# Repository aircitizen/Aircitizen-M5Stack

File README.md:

# m5stack

### Description

Here you'll find the CAD (STL+ F3d) for making your own shield, and the electronic shield (eagle + gerber file)

Component Name | Product link
------------ | -------------
M5 board |  https://amzn.to/2YmzmEy
Battery shield 700mAh  | https://amzn.to/2IX5oBG
Plantower PMSA003 | add link here.

 ###### Credit
Created by Vincent DUPUIS
with participation of :

Adel KHENICHE on Electronic production

Raphael BOYERO on 3D design.

#### Sources

Adafruit SHT31 | https://github.com/adafruit/Adafruit-SHT31-Sensor-Breakout-PCB

Adafruit Si7021 | https://learn.adafruit.com/adafruit-si7021-temperature-plus-humidity-sensor

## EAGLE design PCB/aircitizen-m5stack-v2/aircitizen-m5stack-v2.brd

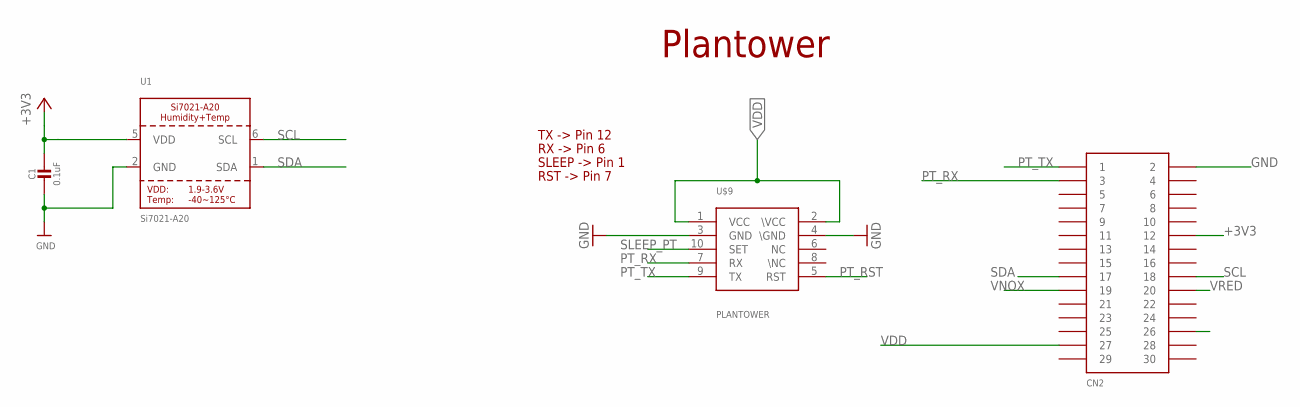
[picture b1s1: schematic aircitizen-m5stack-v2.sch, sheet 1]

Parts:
C1: 0.1uF; _1206
CN2: CON_PINHD-2X15; 2X15SMD
U1: Si7021-A20; DFN6_3X3_SI
U$9: PLANTOWER; CONN

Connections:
+3V3: C1.1, CN2.P$12 (12), U1.5 (VDD)
GND: C1.2, CN2.P$2 (2), U1.2 (GND), U$9.3 (GND), U$9.4 (\GND); also elsewhere on the board
PRE26: CN2.P$26 (26); also elsewhere on the board
PT_RST: U$9.5 (RST)
PT_RX: CN2.P$3 (3), U$9.7 (RX)
PT_TX: CN2.P$1 (1), U$9.9 (TX)
SCL: CN2.P$18 (18), U1.6 (SCL)
SDA: CN2.P$17 (17), U1.1 (SDA)
SLEEP_PT: U$9.10 (SET)
VDD: CN2.P$27 (27), U$9.1 (VCC), U$9.2 (\VCC); also elsewhere on the board
VNOX: CN2.P$19 (19); also elsewhere on the board
VRED: CN2.P$20 (20); also elsewhere on the board

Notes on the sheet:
Plantower
RX -> Pin 6
TX -> Pin 12
SLEEP -> Pin 1
RST -> Pin 7

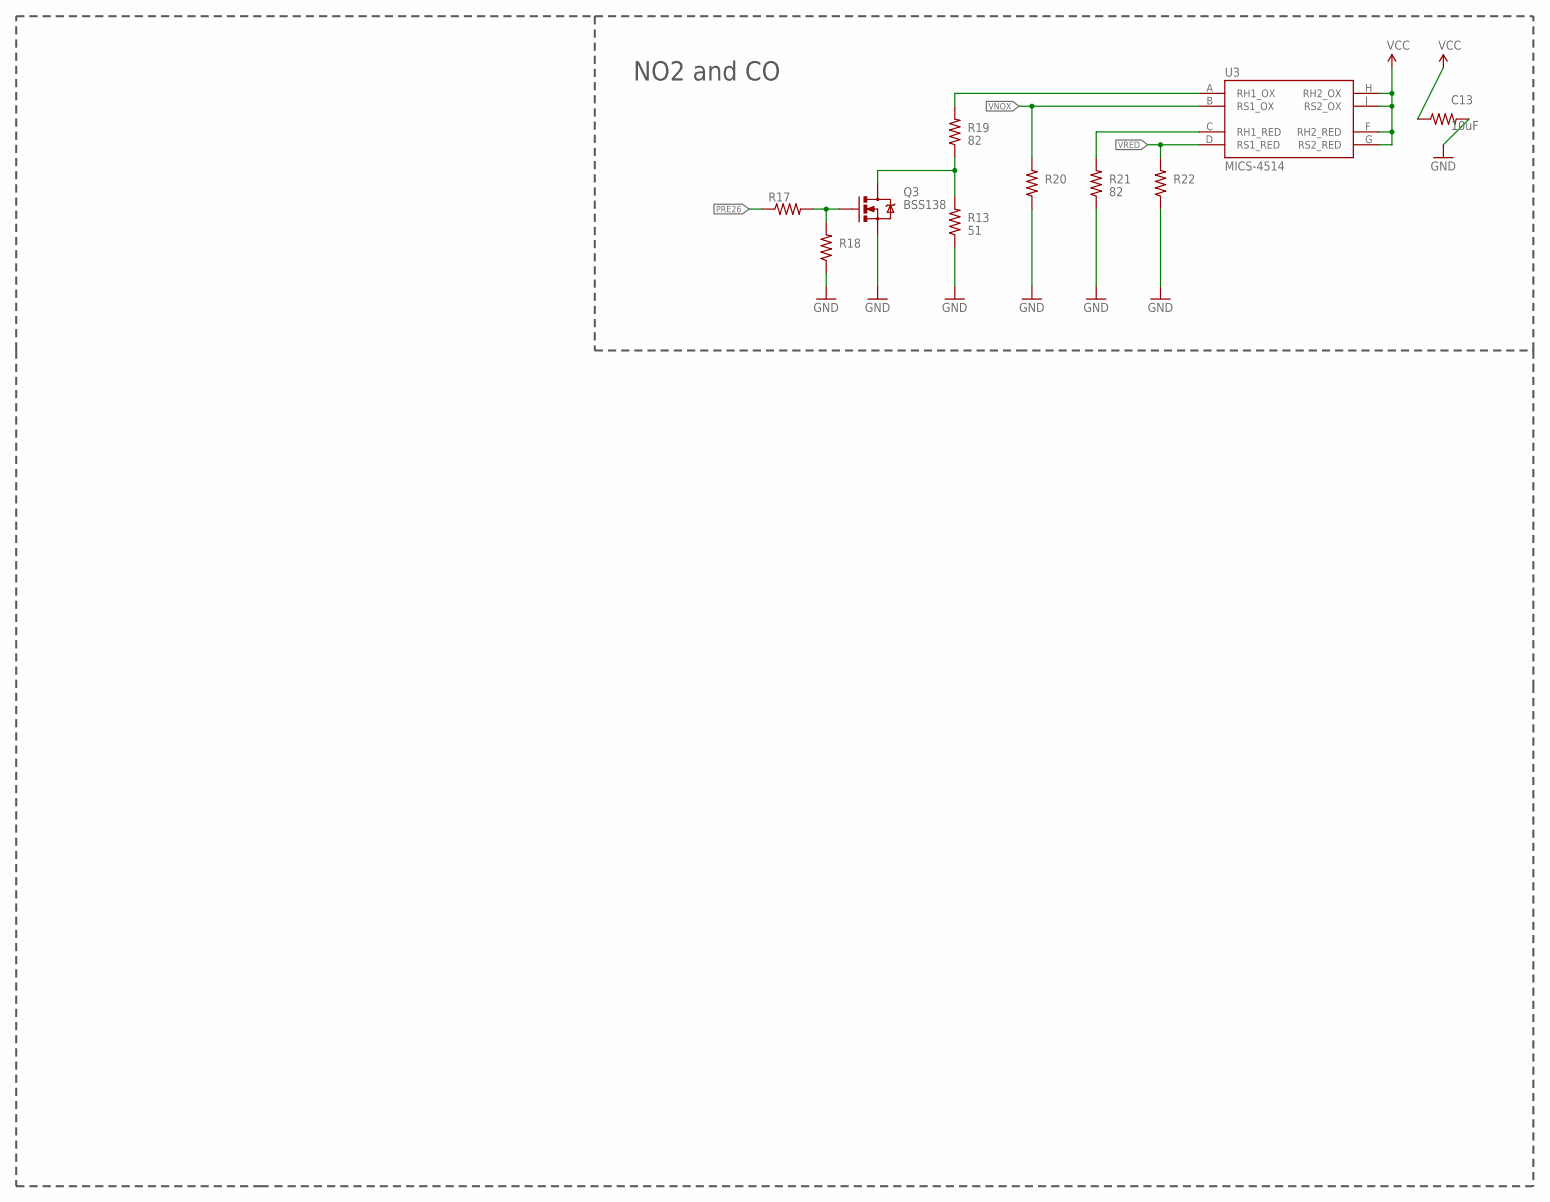
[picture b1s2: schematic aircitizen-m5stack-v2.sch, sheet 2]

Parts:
C13: 10uF; R1206FAB
Q3: MOSFET-NCHANNELBSS138; SOT23-3
R13: 51; R1206FAB
R17: 100; R1206FAB
R18: 100K; R1206FAB
R19, R21: 82; R1206FAB
R20: 22K; R1206FAB
R22: 47K; R1206FAB
U3: MICS-4514; MICS_10-SMD

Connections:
GND: C13.2, Q3.2 (S), R13.1, R18.1, R20.1, R21.1, R22.1; also elsewhere on the board
unnamed: Q3.3 (D), R13.2, R19.1
unnamed: Q3.1 (G), R17.2, R18.2
unnamed: R19.2, U3.A (RH1_OX)
unnamed: R21.2, U3.C (RH1_RED)
PRE26: R17.1; also elsewhere on the board
VDD: C13.1, U3.F (RH2_RED), U3.G (RS2_RED), U3.H (RH2_OX), U3.J (RS2_OX); also elsewhere on the board
VNOX: R20.2, U3.B (RS1_OX); also elsewhere on the board
VRED: R22.2, U3.D (RS1_RED); also elsewhere on the board

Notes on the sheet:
NO2 and CO

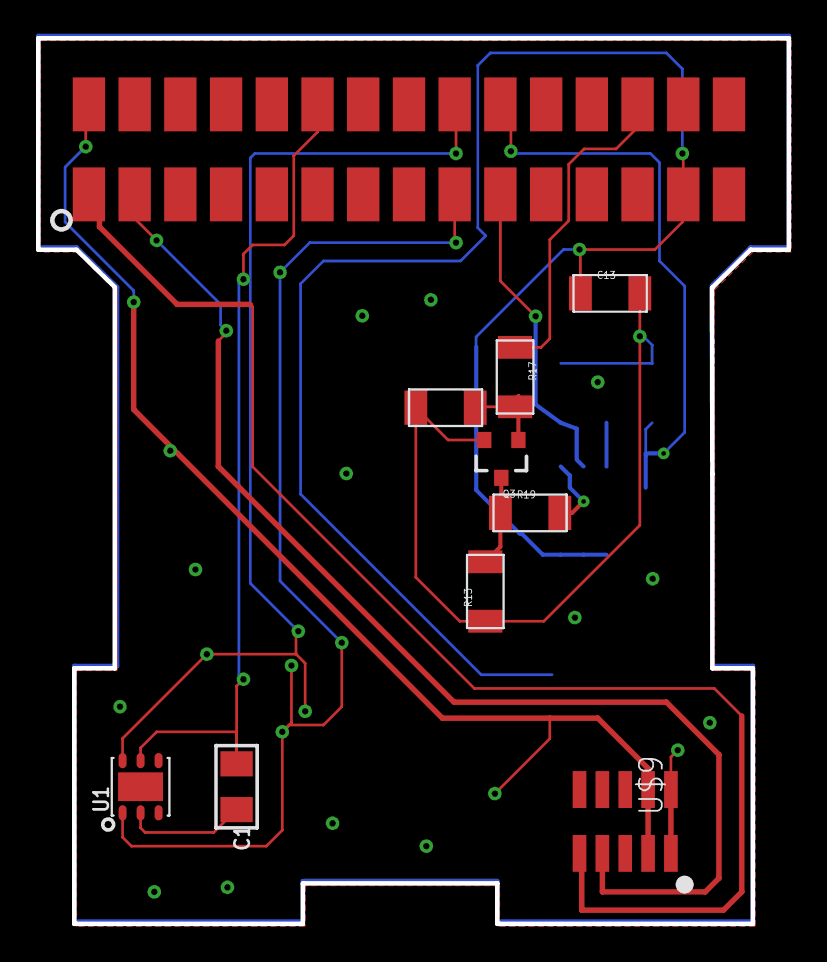
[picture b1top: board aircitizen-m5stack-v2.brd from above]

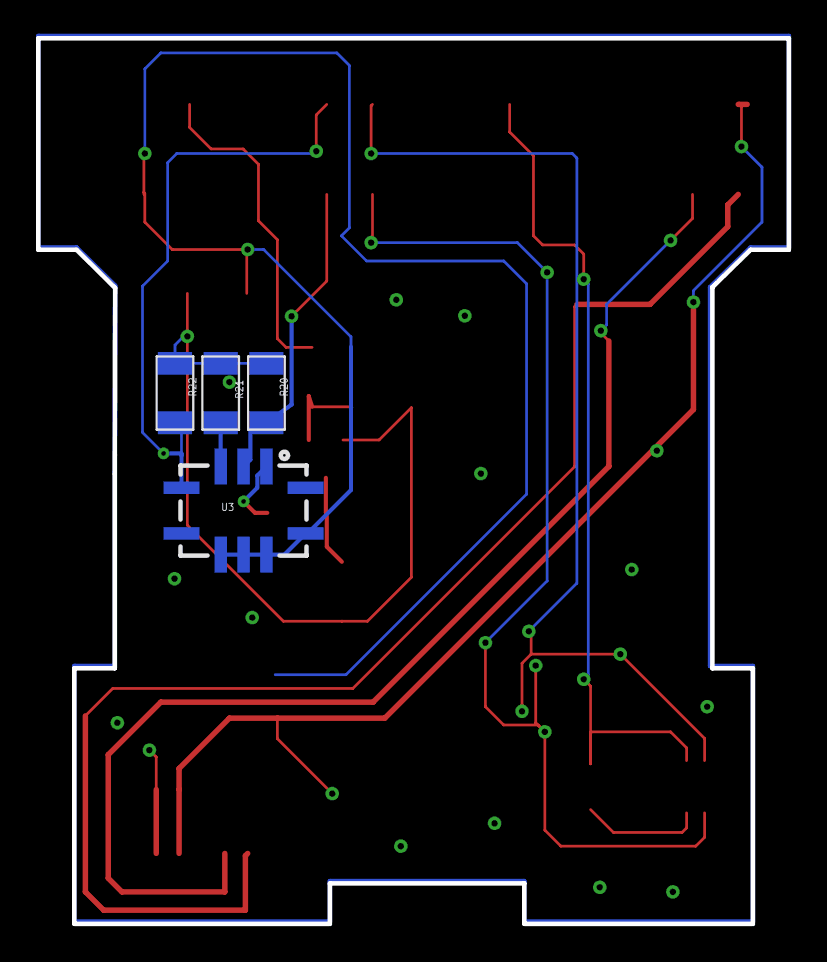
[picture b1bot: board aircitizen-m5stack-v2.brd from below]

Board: 2 copper layers, 41.7 x 49.2 mm, 14 parts (4 on the bottom side), 14 nets.

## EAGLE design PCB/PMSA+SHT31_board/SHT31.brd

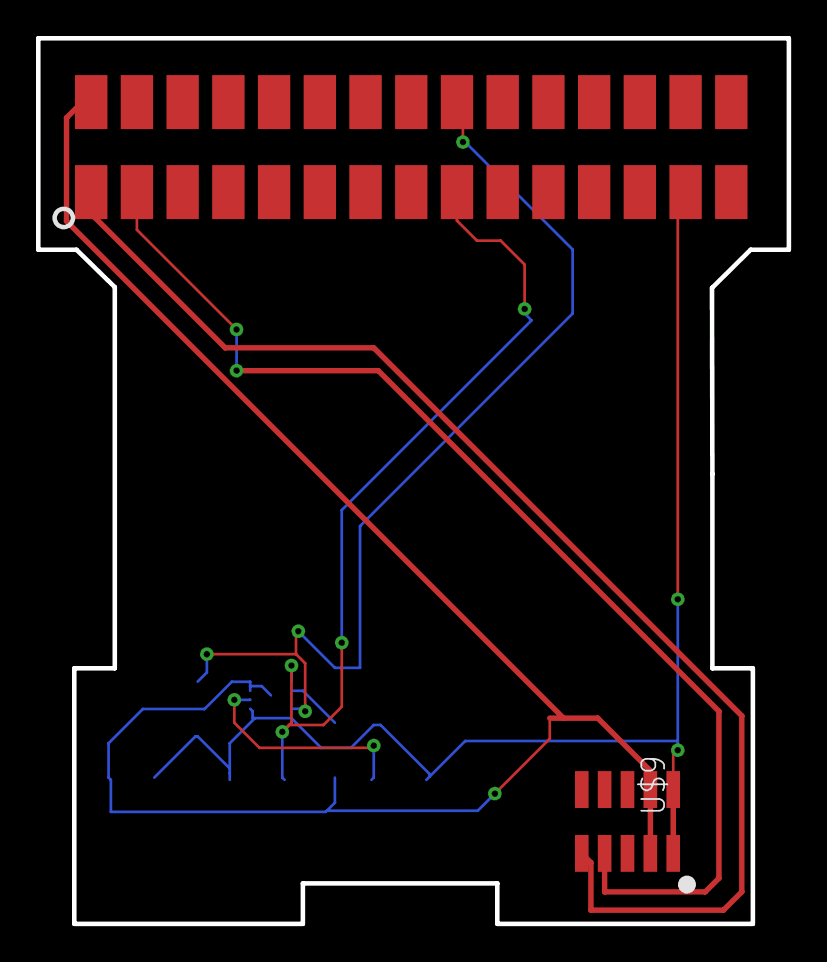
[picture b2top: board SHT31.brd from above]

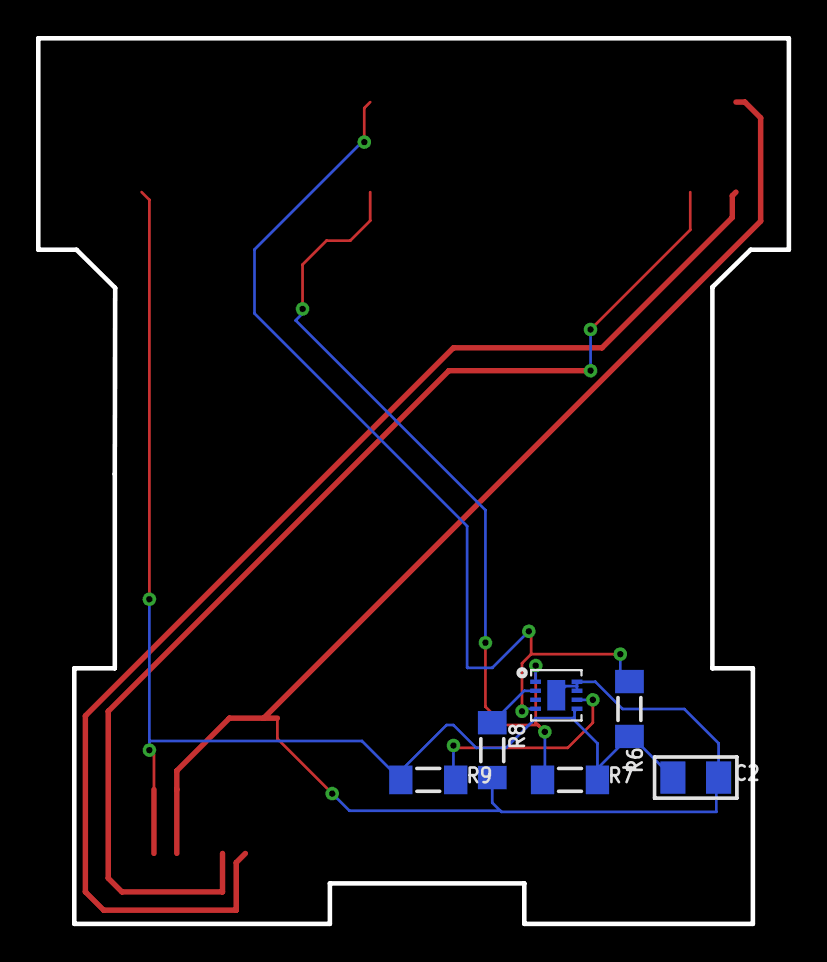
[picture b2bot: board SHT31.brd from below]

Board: 2 copper layers, 41.7 x 49.2 mm, 8 parts (6 on the bottom side), 8 nets.

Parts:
C2: 10uF; _1206
CN2: CON_PINHD-2X15; 2X15SMD
R6, R7, R8, R9: 10K; _1206MP
U2: SHT31-DIS; SHT3X
U$9: PLANTOWER; CONN

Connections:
ADDR: R8.1, U2.2
GND: C2.2, CN2.P$2, R8.2, U2.7, U2.8, U2.THERMAL, U$9.3, U$9.4
PT_RX: CN2.P$3, U$9.7
PT_TX: CN2.P$1, U$9.9
RST: R9.2, U2.6
SCL: CN2.P$18, R6.1, U2.4
SDA: CN2.P$17, R7.1, U2.1
VDD: C2.1, CN2.P$27, R6.2, R7.2, R9.1, U2.5, U$9.1, U$9.2

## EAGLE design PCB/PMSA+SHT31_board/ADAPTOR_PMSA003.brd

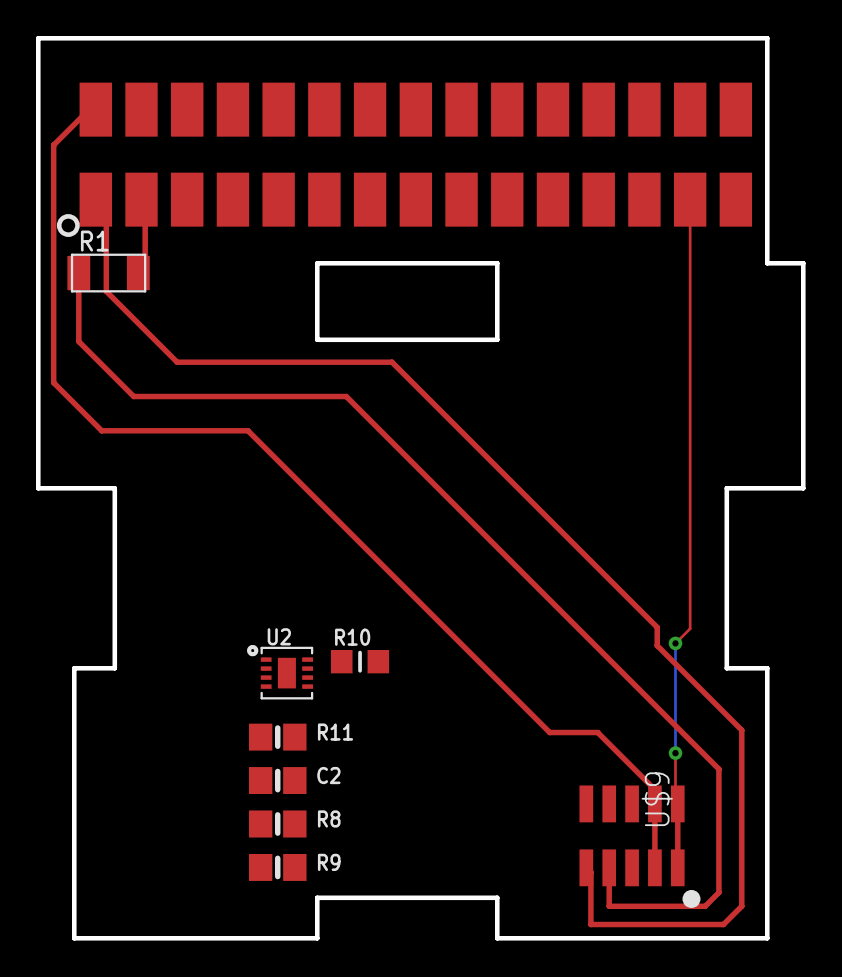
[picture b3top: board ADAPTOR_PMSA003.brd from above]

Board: 2 copper layers, 42.5 x 50.0 mm, 9 parts (0 on the bottom side), 9 nets.

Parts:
C2: 10uF; 0805-NO
CN2: CON_PINHD-2X15; 2X15SMD
R1: R1206FAB
R8, R9, R11: 10K; 0805-NO
R10: 10K; _0805MP
U2: SHT31-DIS; SHT3X
U$9: PLANTOWER; CONN

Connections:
ADDR: R10.1, U2.2
DELETE: CN2.P$3, R1.2
GND: C2.2, CN2.P$2, R10.2, U2.7, U2.8, U2.THERMAL, U$9.3, U$9.4
PT_RX: R1.1, U$9.7
PT_TX: CN2.P$1, U$9.9
RST: R11.2, U2.6
SCL: R8.1, U2.4
SDA: R9.1, U2.1
VCC: C2.1, CN2.P$27, R8.2, R9.2, R11.1, U2.5, U$9.1, U$9.2

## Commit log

2019-06-30 test upload
2019-07-02 clean up and add pcb
2019-07-02 change readme
2019-07-03 suppression ai.file
2019-07-03 adding adafruit source file
2019-07-08 cp sht31
2019-07-08 insertion NOX & CO Captor
2019-07-08 add amigo proto
2019-07-08 pcbV2 ready to go!
2019-07-08 3DPACKAGE!
2019-10-29 change Temp and RH sensor
2019-10-29 add new pcb
2019-10-29 add pcvb
2019-10-29 add source file
2019-10-29 Nouvel version pcb V2
2019-10-29 version pcb #2

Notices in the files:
parts and their libraries:
microbuilder: This work is placed in the public domain, and may be freely used for commercial and non-commercial work with the following conditions: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
SparkFun-DiscreteSemi: Licensing: Creative Commons ShareAlike 4.0 International - https://creativecommons.org/licenses/by-sa/4.0
